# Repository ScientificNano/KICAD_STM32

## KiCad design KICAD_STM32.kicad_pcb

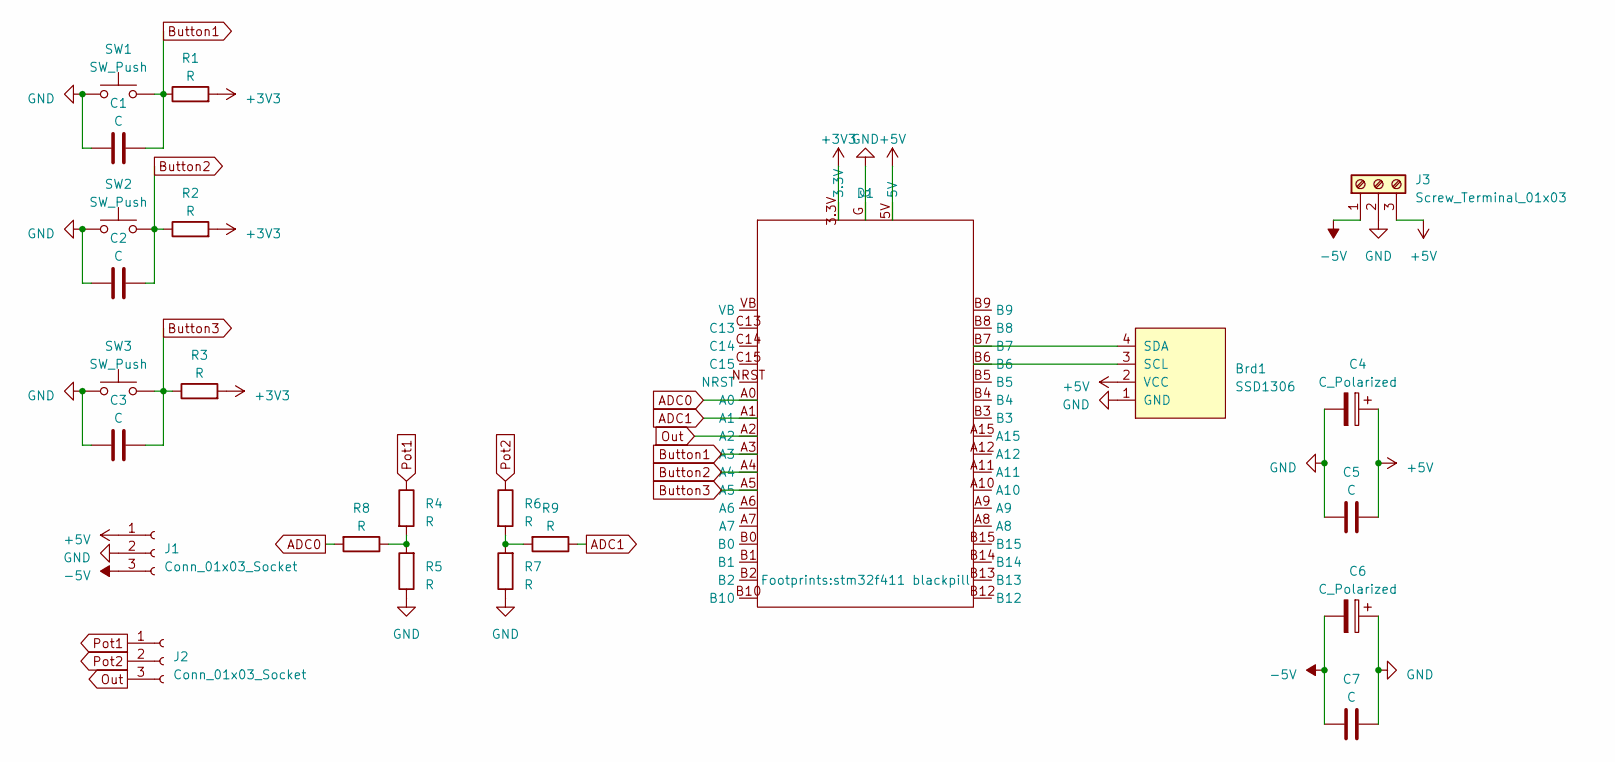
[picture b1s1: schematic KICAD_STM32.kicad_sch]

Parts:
Brd1: SSD1306; 128x64OLED
C1, C2, C3, C5, C7: C; C_0805_2012Metric_Pad1.18x1.45mm_HandSolder
C4, C6: C_Polarized; CP_EIA-3216-18_Kemet-A_Pad1.58x1.35mm_HandSolder
D1: stm32f411 blackpill
J1, J2: Conn_01x03_Socket; PinSocket_1x03_P2.54mm_Vertical
J3: Screw_Terminal_01x03; TerminalBlock_bornier-3_P5.08mm
R1, R2, R3, R4, R5, R6, R7, R8, R9: R; R_1206_3216Metric_Pad1.30x1.75mm_HandSolder
SW1, SW2, SW3: SW_Push; SW_SPST_SKQG_WithStem

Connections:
+3V3: D1.3.3V, R1.2, R2.2, R3.2
+5V: Brd1.2 (VCC), C4.1, C5.2, D1.5V, J1.1, J3.3
-5V: C6.2, C7.2, J1.3, J3.1
ADC0: D1.A0, R8.2
ADC1: D1.A1, R9.1
Button1: C1.2, D1.A3, R1.1, SW1.2
Button2: C2.2, D1.A4, R2.1, SW2.2
Button3: C3.2, D1.A5, R3.1, SW3.2
GND: Brd1.1 (GND), C1.1, C2.1, C3.1, C4.2, C5.1, C6.1, C7.1, D1.G, J1.2, J3.2, R5.1, R7.1, SW1.1, SW2.1, SW3.1
unnamed: Brd1.3 (SCL), D1.B6
unnamed: Brd1.4 (SDA), D1.B7
unnamed: R4.2, R5.2, R8.1
unnamed: R6.2, R7.2, R9.2
Out: D1.A2, J2.3
Pot1: J2.1, R4.1
Pot2: J2.2, R6.1

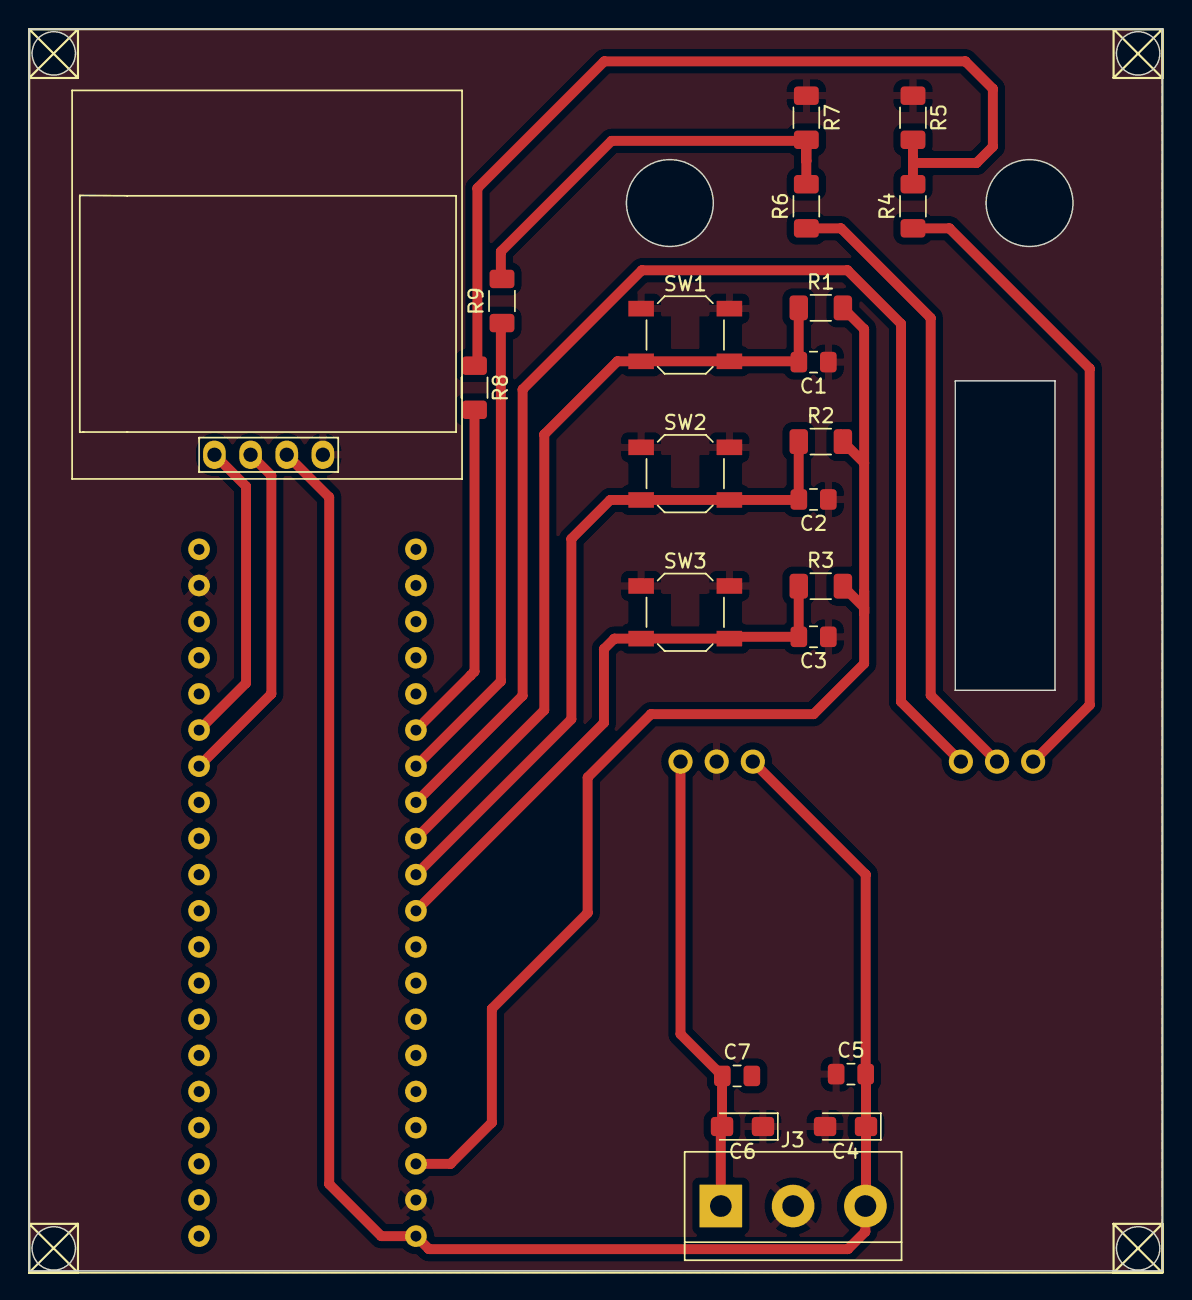
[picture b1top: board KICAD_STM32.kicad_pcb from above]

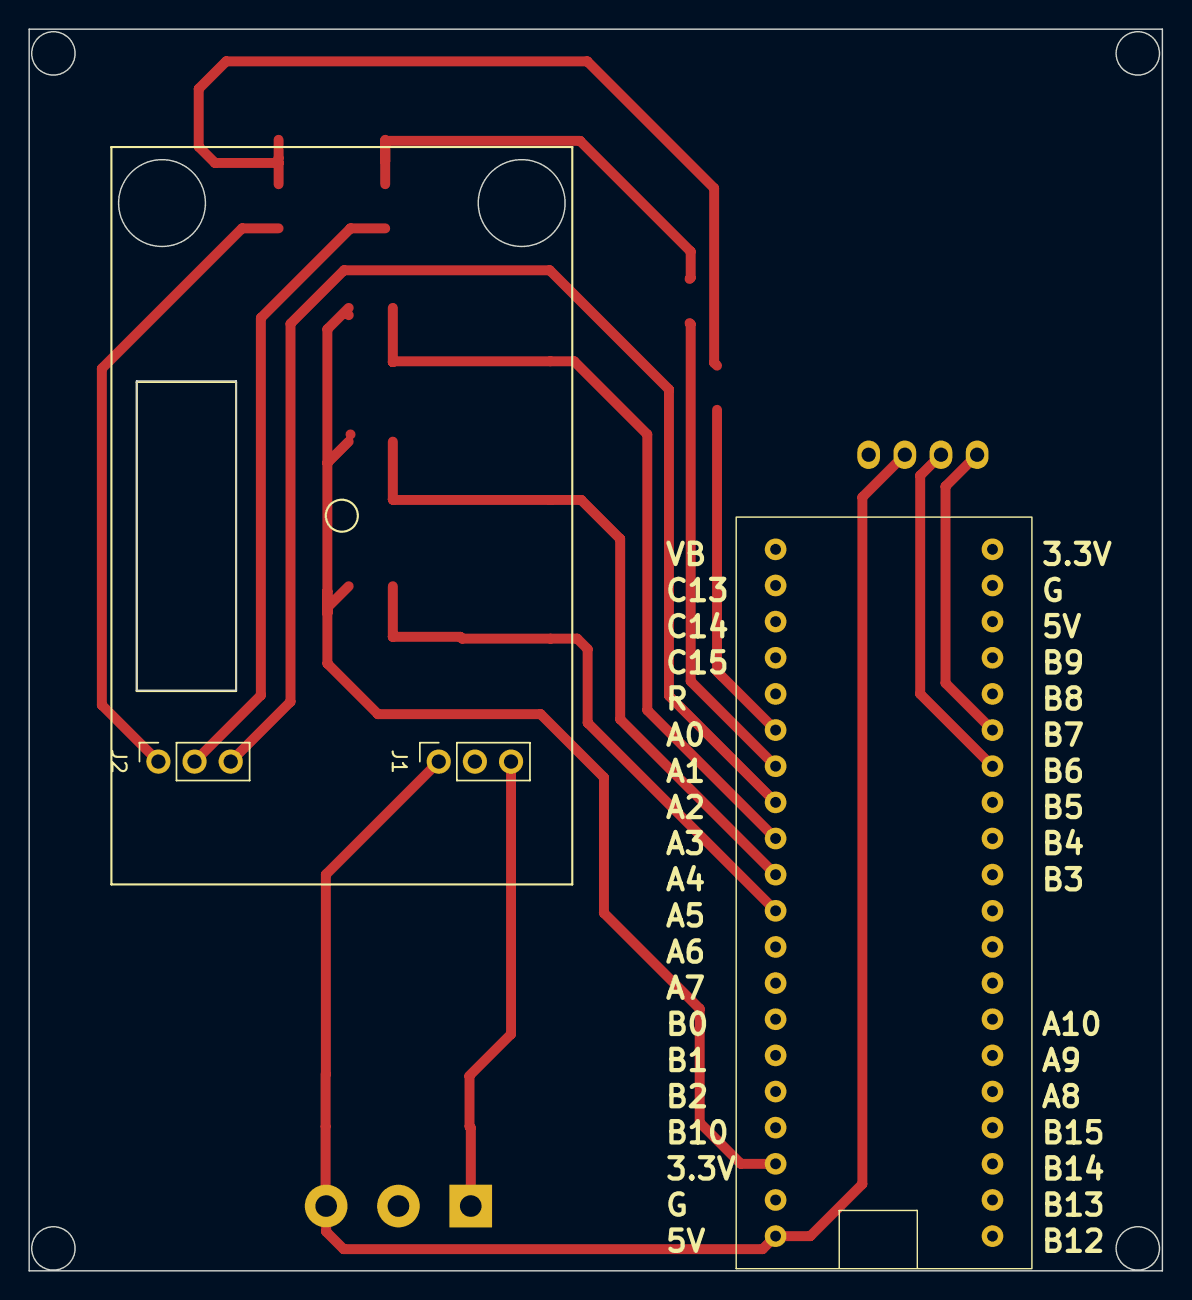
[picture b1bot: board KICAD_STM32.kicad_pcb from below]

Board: 2 copper layers, 79.6 x 87.2 mm, 24 parts (3 on the bottom side), 16 nets.

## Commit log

2023-11-25 PCB and Schematic
2023-11-26 fixed errors in the board trace
2023-11-27 add new resistor
